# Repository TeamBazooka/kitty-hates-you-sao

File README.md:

# Kitty Shitty add-on

## BOM
1. [LED](https://www.digikey.com/product-detail/en/osram-opto-semiconductors-inc/LY-T776-R1S2-26-Z/475-1149-1-ND/808919)
2. Resistor, pick one you like
3. 0.1" pin headers can be had places.

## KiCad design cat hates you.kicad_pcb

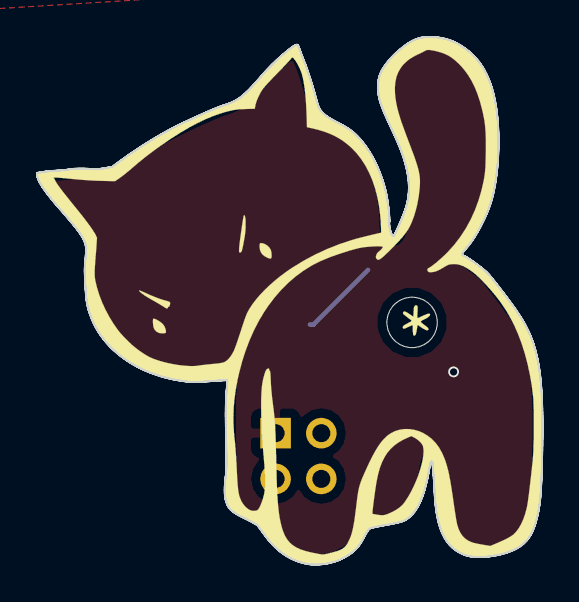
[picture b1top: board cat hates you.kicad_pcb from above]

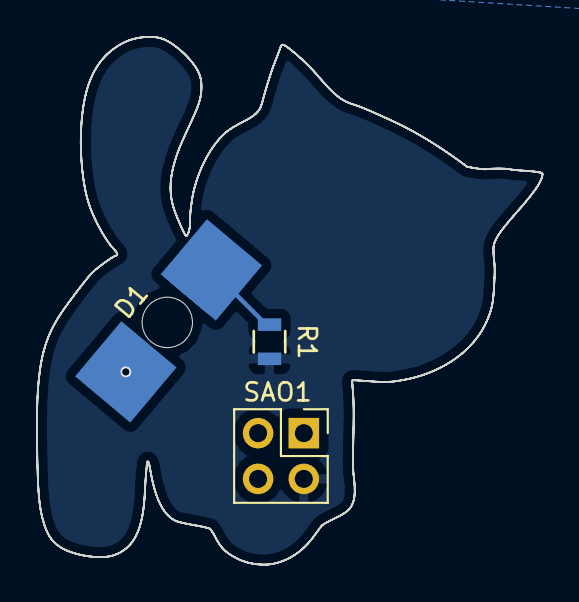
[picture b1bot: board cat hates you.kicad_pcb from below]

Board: 2 copper layers, 28.1 x 29.3 mm, 3 parts (3 on the bottom side), 3 nets.

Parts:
D1: LED
R1: 220R; R_0805
SAO1: Conn_02x02_Counter_Clockwise; Pin_Header_Straight_2x02_Pitch2.54mm

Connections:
+3V3: D1.2, SAO1.1
GND: R1.2, SAO1.2
unnamed: D1.1, R1.1

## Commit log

2018-07-31 intial commit
2018-07-31 Add readme
